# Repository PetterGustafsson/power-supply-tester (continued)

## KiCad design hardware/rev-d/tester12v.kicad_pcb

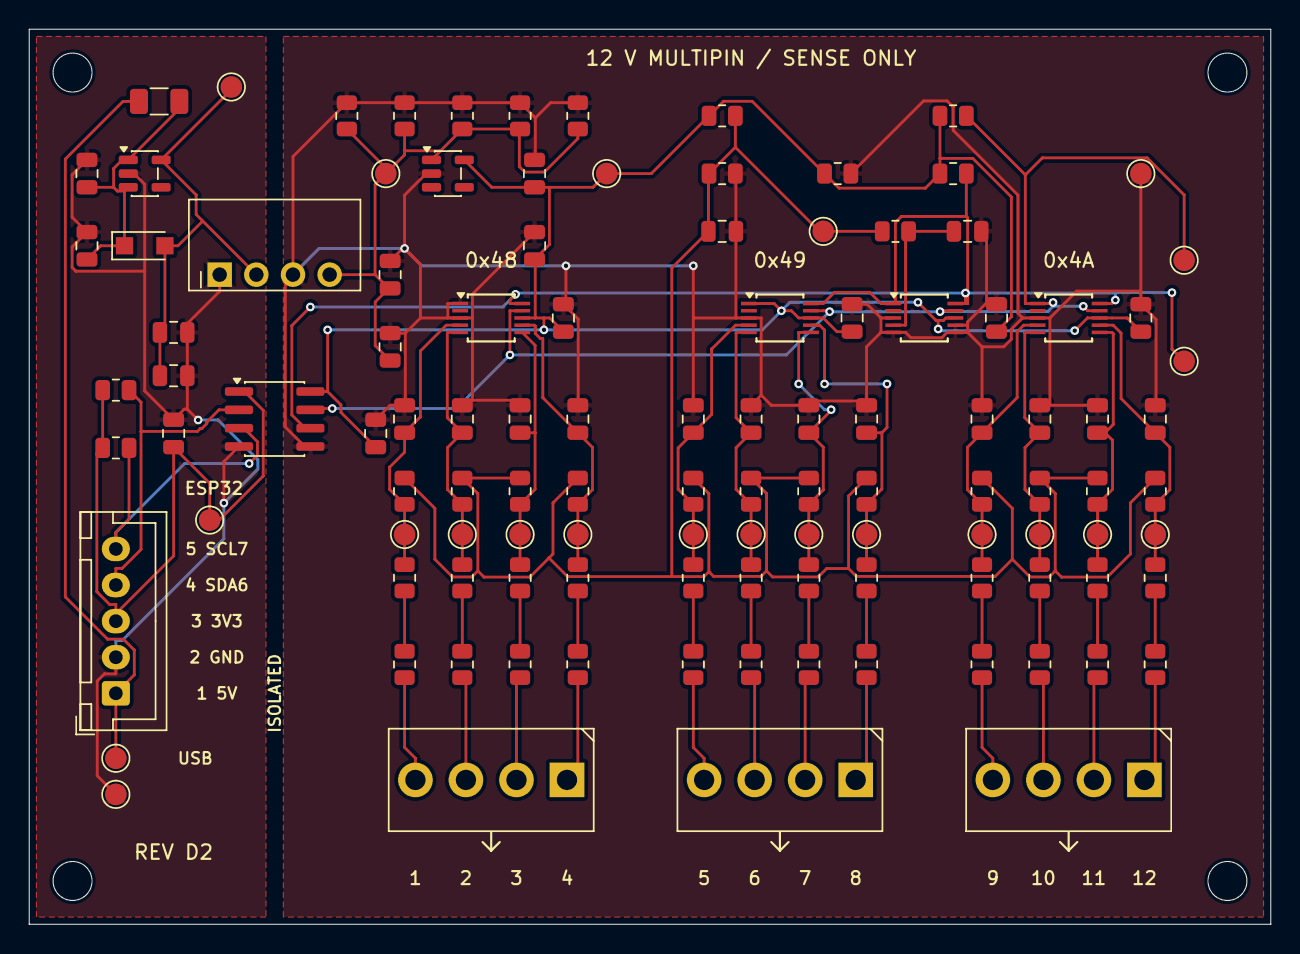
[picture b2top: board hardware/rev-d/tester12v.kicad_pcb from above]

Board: 2 copper layers, 86.0 x 62.0 mm, 117 parts (0 on the bottom side), 50 nets.

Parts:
C1, C2, C3, C4, C5, C6, C7, C8, C9, C10, C11, C12, C26, C28: 470p; C_0805_2012Metric
C13, C14, C15, C17, C19, C21, C23, C24, C25, C27: 100n; C_0805_2012Metric
C16, C18, C20, C22: 10u; C_0805_2012Metric
D1: LDO reverse protection; Nexperia_CFP3_SOD-123W
F1: 250mA PTC; Fuse_1206_3216Metric
H1, H2, H3, H4: MountingHole_2.7mm_M2.5
J1: INPUTS 1-4; XY350V_3.5_4P
J2: INPUTS 5-8; XY350V_3.5_4P
J3: INPUTS 9-12; XY350V_3.5_4P
J4: DISPLAY HARNESS; JST_XH_B5B-XH-A_1x05_P2.50mm_Vertical
R1, R2, R4, R5, R7, R8, R10, R11, R13, R14, R16, R17, R19, R20, R22, R23, R25, R26, R28, R29, R31, R32, R34, R35: 1M; R_0805_2012Metric
R3, R6, R9, R12, R15, R18, R21, R24, R27, R30, R33, R36, R37, R44, R45, R46, R47, R49: 4.7k; R_0805_2012Metric
R38, R39, R40, R41, R42, R43, R48: 1k; R_0805_2012Metric
TP1: A1; TestPoint_Pad_D1.5mm
TP2: A2; TestPoint_Pad_D1.5mm
TP3: A3; TestPoint_Pad_D1.5mm
TP4: A4; TestPoint_Pad_D1.5mm
TP5: A5; TestPoint_Pad_D1.5mm
TP6: A6; TestPoint_Pad_D1.5mm
TP7: A7; TestPoint_Pad_D1.5mm
TP8: A8; TestPoint_Pad_D1.5mm
TP9: A9; TestPoint_Pad_D1.5mm
TP10: A10; TestPoint_Pad_D1.5mm
TP11: A11; TestPoint_Pad_D1.5mm
TP12: A12; TestPoint_Pad_D1.5mm
TP13: USB5V; TestPoint_Pad_D1.5mm
TP14: USB_GND; TestPoint_Pad_D1.5mm
TP15: HOST3V3; TestPoint_Pad_D1.5mm
TP16: P3V3; TestPoint_Pad_D1.5mm
TP17: ISO5V_RAW; TestPoint_Pad_D1.5mm
TP18: A3V3; TestPoint_Pad_D1.5mm
TP19: AGND; TestPoint_Pad_D1.5mm
TP20: VBIAS; TestPoint_Pad_D1.5mm
TP21: SDA_ISO; TestPoint_Pad_D1.5mm
TP22: SCL_ISO; TestPoint_Pad_D1.5mm
U1, U2, U3, U8: ADS1115IDGSR; TSSOP-10_3x3mm_P0.5mm
U4: TLV75533PDBVR; SOT-23-5
U5: TPS70933DBVR; SOT-23-5
U6: ISO1640BDR; SOIC-8_3.9x4.9mm_P1.27mm
U7: B0305S-1WR3; B0305S_1WR3_EVISUN

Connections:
A1: C1.1, R2.2, R3.1, TP1.1, U1.4
A2: C2.1, R5.2, R6.1, TP2.1, U1.5
A3: C3.1, R8.2, R9.1, TP3.1, U1.6
A3V3: C13.1, C14.1, C15.1, C22.1, C23.1, C25.1, C27.1, R37.1, R44.1, R45.1, R48.1, TP18.1, U1.8, U2.1, U2.8, U3.8, U5.5, U6.8, U8.8
A4: C4.1, R11.2, R12.1, TP4.1, U1.7
A5: C5.1, R14.2, R15.1, TP5.1, U2.4
A6: C6.1, R17.2, R18.1, TP6.1, U2.5
A7: C7.1, R20.2, R21.1, TP7.1, U2.6
A8: C8.1, R23.2, R24.1, TP8.1, U2.7
A9: C9.1, R26.2, R27.1, TP9.1, U3.4
A10: C10.1, R29.2, R30.1, TP10.1, U3.5
A11: C11.1, R32.2, R33.1, TP11.1, U3.6
A12: C12.1, R35.2, R36.1, TP12.1, U3.7
AGND: C1.2, C2.2, C3.2, C4.2, C5.2, C6.2, C7.2, C8.2, C9.2, C10.2, C11.2, C12.2, C13.2, C14.2, C15.2, C20.2, C21.2, C22.2, C23.2, C25.2, C26.2, C27.2, C28.2, R38.2, R39.2, R40.2, R41.2, R42.2, R43.2, R48.2, TP19.1, U1.1, U1.3, U2.3, U3.3, U5.2, U6.5, U7.3, U8.3, U8.5, U8.6, U8.7
HOST3V3: C24.1, J4.3, R46.1, R47.1, TP15.1, U6.1
ISO5V_RAW: C20.1, C21.1, R39.1, R40.1, R41.1, R42.1, R43.1, TP17.1, U5.1, U7.4
MID1: R1.2, R2.1
MID2: R4.2, R5.1
MID3: R7.2, R8.1
MID4: R10.2, R11.1
MID5: R13.2, R14.1
MID6: R16.2, R17.1
MID7: R19.2, R20.1
MID8: R22.2, R23.1
MID9: R25.2, R26.1
MID10: R28.2, R29.1
MID11: R31.2, R32.1
MID12: R34.2, R35.1
P1: J1.4, R1.1
P2: J1.3, R4.1
P3: J1.2, R7.1
P3V3: C18.1, C19.1, D1.2, TP16.1, U4.5, U7.2
P4: J1.1, R10.1
P5: J2.4, R13.1
P6: J2.3, R16.1
P7: J2.2, R19.1
P8: J2.1, R22.1
P9: J3.4, R25.1
P10: J3.3, R28.1
P11: J3.2, R31.1
P12: J3.1, R34.1
REF_ADC: C28.1, R49.2, U8.4
SCL_HOST: J4.5, R47.2, U6.3
SCL_ISO: R45.2, TP22.1, U1.10, U2.10, U3.10, U6.6, U8.1, U8.10
SDA_HOST: J4.4, R46.2, U6.2
SDA_ISO: R44.2, TP21.1, U1.9, U2.9, U3.1, U3.9, U6.7, U8.9
USB5V: F1.1, J4.1, TP13.1
USB5V_F: C16.1, C17.1, D1.1, F1.2, U4.1, U4.3
USB_GND: C16.2, C17.2, C18.2, C19.2, C24.2, J4.2, TP14.1, U4.2, U6.4, U7.1
VBIAS: C26.1, R3.2, R6.2, R9.2, R12.2, R15.2, R18.2, R21.2, R24.2, R27.2, R30.2, R33.2, R36.2, R37.2, R38.1, R49.1, TP20.1

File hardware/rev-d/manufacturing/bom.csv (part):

Reference,Value,Manufacturer,MPN,Footprint,Populate,Notes,LCSC,JLC Category
J1,INPUTS 1-4,Ningbo Xinlaiya Elec.,XY350V-3.5-4P,Tester:XY350V_3.5_4P,YES,"C557656; 3.5mm pitch, 0.8mm square pins, 1.4mm drill. 14x6.9mm body. WIRE OPENINGS FACE LOWER BOARD EDGE (+Y); footprint contact 1 at right. Input labels increase left-to-right.",C557656,Extended
R1,1M,UNI-ROYAL,0805W8F1004T5E,Tester:R_0805_2012Metric,YES,1%,C17514,Basic
R2,1M,UNI-ROYAL,0805W8F1004T5E,Tester:R_0805_2012Metric,YES,1%,C17514,Basic
R3,4.7k,UNI-ROYAL,0805W8F4701T5E,Tester:R_0805_2012Metric,YES,"1% | JLC: Basic; same 1%, 100ppm/K, 125mW, 150V rating",C17673,Basic
C1,470p,Fenghua,0805B471K500NT,Tester:C_0805_2012Metric,YES,"470pF +/-10%, 50V X7R; Rev D candidate model bounds total input capacitance at 1nF",C1743,Basic
R4,1M,UNI-ROYAL,0805W8F1004T5E,Tester:R_0805_2012Metric,YES,1%,C17514,Basic
R5,1M,UNI-ROYAL,0805W8F1004T5E,Tester:R_0805_2012Metric,YES,1%,C17514,Basic
R6,4.7k,UNI-ROYAL,0805W8F4701T5E,Tester:R_0805_2012Metric,YES,"1% | JLC: Basic; same 1%, 100ppm/K, 125mW, 150V rating",C17673,Basic
C2,470p,Fenghua,0805B471K500NT,Tester:C_0805_2012Metric,YES,"470pF +/-10%, 50V X7R; Rev D candidate model bounds total input capacitance at 1nF",C1743,Basic
R7,1M,UNI-ROYAL,0805W8F1004T5E,Tester:R_0805_2012Metric,YES,1%,C17514,Basic
R8,1M,UNI-ROYAL,0805W8F1004T5E,Tester:R_0805_2012Metric,YES,1%,C17514,Basic
R9,4.7k,UNI-ROYAL,0805W8F4701T5E,Tester:R_0805_2012Metric,YES,"1% | JLC: Basic; same 1%, 100ppm/K, 125mW, 150V rating",C17673,Basic
C3,470p,Fenghua,0805B471K500NT,Tester:C_0805_2012Metric,YES,"470pF +/-10%, 50V X7R; Rev D candidate model bounds total input capacitance at 1nF",C1743,Basic
R10,1M,UNI-ROYAL,0805W8F1004T5E,Tester:R_0805_2012Metric,YES,1%,C17514,Basic
R11,1M,UNI-ROYAL,0805W8F1004T5E,Tester:R_0805_2012Metric,YES,1%,C17514,Basic
R12,4.7k,UNI-ROYAL,0805W8F4701T5E,Tester:R_0805_2012Metric,YES,"1% | JLC: Basic; same 1%, 100ppm/K, 125mW, 150V rating",C17673,Basic
C4,470p,Fenghua,0805B471K500NT,Tester:C_0805_2012Metric,YES,"470pF +/-10%, 50V X7R; Rev D candidate model bounds total input capacitance at 1nF",C1743,Basic
U1,ADS1115IDGSR,Texas Instruments,ADS1115IDGSR,Tester:TSSOP-10_3x3mm_P0.5mm,YES,"PGA +/-1.024V, nominal attenuation 426.5319. Rev D calibration/firmware required.",C37593,Extended
C13,100n,Yageo,CC0805KRX7R9BB104,Tester:C_0805_2012Metric,YES,"Use specified capacitance, voltage and dielectric | JLC: Basic; 100nF, 10%, 50V, X7R preserved",C49678,Basic
J2,INPUTS 5-8,Ningbo Xinlaiya Elec.,XY350V-3.5-4P,Tester:XY350V_3.5_4P,YES,"C557656; 3.5mm pitch, 0.8mm square pins, 1.4mm drill. 14x6.9mm body. WIRE OPENINGS FACE LOWER BOARD EDGE (+Y); footprint contact 1 at right. Input labels increase left-to-right.",C557656,Extended
R13,1M,UNI-ROYAL,0805W8F1004T5E,Tester:R_0805_2012Metric,YES,1%,C17514,Basic
R14,1M,UNI-ROYAL,0805W8F1004T5E,Tester:R_0805_2012Metric,YES,1%,C17514,Basic
R15,4.7k,UNI-ROYAL,0805W8F4701T5E,Tester:R_0805_2012Metric,YES,"1% | JLC: Basic; same 1%, 100ppm/K, 125mW, 150V rating",C17673,Basic
C5,470p,Fenghua,0805B471K500NT,Tester:C_0805_2012Metric,YES,"470pF +/-10%, 50V X7R; Rev D candidate model bounds total input capacitance at 1nF",C1743,Basic
R16,1M,UNI-ROYAL,0805W8F1004T5E,Tester:R_0805_2012Metric,YES,1%,C17514,Basic
R17,1M,UNI-ROYAL,0805W8F1004T5E,Tester:R_0805_2012Metric,YES,1%,C17514,Basic
R18,4.7k,UNI-ROYAL,0805W8F4701T5E,Tester:R_0805_2012Metric,YES,"1% | JLC: Basic; same 1%, 100ppm/K, 125mW, 150V rating",C17673,Basic
C6,470p,Fenghua,0805B471K500NT,Tester:C_0805_2012Metric,YES,"470pF +/-10%, 50V X7R; Rev D candidate model bounds total input capacitance at 1nF",C1743,Basic
R19,1M,UNI-ROYAL,0805W8F1004T5E,Tester:R_0805_2012Metric,YES,1%,C17514,Basic
R20,1M,UNI-ROYAL,0805W8F1004T5E,Tester:R_0805_2012Metric,YES,1%,C17514,Basic
R21,4.7k,UNI-ROYAL,0805W8F4701T5E,Tester:R_0805_2012Metric,YES,"1% | JLC: Basic; same 1%, 100ppm/K, 125mW, 150V rating",C17673,Basic
C7,470p,Fenghua,0805B471K500NT,Tester:C_0805_2012Metric,YES,"470pF +/-10%, 50V X7R; Rev D candidate model bounds total input capacitance at 1nF",C1743,Basic
R22,1M,UNI-ROYAL,0805W8F1004T5E,Tester:R_0805_2012Metric,YES,1%,C17514,Basic
R23,1M,UNI-ROYAL,0805W8F1004T5E,Tester:R_0805_2012Metric,YES,1%,C17514,Basic
R24,4.7k,UNI-ROYAL,0805W8F4701T5E,Tester:R_0805_2012Metric,YES,"1% | JLC: Basic; same 1%, 100ppm/K, 125mW, 150V rating",C17673,Basic
C8,470p,Fenghua,0805B471K500NT,Tester:C_0805_2012Metric,YES,"470pF +/-10%, 50V X7R; Rev D candidate model bounds total input capacitance at 1nF",C1743,Basic
U2,ADS1115IDGSR,Texas Instruments,ADS1115IDGSR,Tester:TSSOP-10_3x3mm_P0.5mm,YES,"PGA +/-1.024V, nominal attenuation 426.5319. Rev D calibration/firmware required.",C37593,Extended
C14,100n,Yageo,CC0805KRX7R9BB104,Tester:C_0805_2012Metric,YES,"Use specified capacitance, voltage and dielectric | JLC: Basic; 100nF, 10%, 50V, X7R preserved",C49678,Basic
J3,INPUTS 9-12,Ningbo Xinlaiya Elec.,XY350V-3.5-4P,Tester:XY350V_3.5_4P,YES,"C557656; 3.5mm pitch, 0.8mm square pins, 1.4mm drill. 14x6.9mm body. WIRE OPENINGS FACE LOWER BOARD EDGE (+Y); footprint contact 1 at right. Input labels increase left-to-right.",C557656,Extended
R25,1M,UNI-ROYAL,0805W8F1004T5E,Tester:R_0805_2012Metric,YES,1%,C17514,Basic
R26,1M,UNI-ROYAL,0805W8F1004T5E,Tester:R_0805_2012Metric,YES,1%,C17514,Basic
R27,4.7k,UNI-ROYAL,0805W8F4701T5E,Tester:R_0805_2012Metric,YES,"1% | JLC: Basic; same 1%, 100ppm/K, 125mW, 150V rating",C17673,Basic
C9,470p,Fenghua,0805B471K500NT,Tester:C_0805_2012Metric,YES,"470pF +/-10%, 50V X7R; Rev D candidate model bounds total input capacitance at 1nF",C1743,Basic
R28,1M,UNI-ROYAL,0805W8F1004T5E,Tester:R_0805_2012Metric,YES,1%,C17514,Basic
R29,1M,UNI-ROYAL,0805W8F1004T5E,Tester:R_0805_2012Metric,YES,1%,C17514,Basic
R30,4.7k,UNI-ROYAL,0805W8F4701T5E,Tester:R_0805_2012Metric,YES,"1% | JLC: Basic; same 1%, 100ppm/K, 125mW, 150V rating",C17673,Basic
C10,470p,Fenghua,0805B471K500NT,Tester:C_0805_2012Metric,YES,"470pF +/-10%, 50V X7R; Rev D candidate model bounds total input capacitance at 1nF",C1743,Basic
R31,1M,UNI-ROYAL,0805W8F1004T5E,Tester:R_0805_2012Metric,YES,1%,C17514,Basic
R32,1M,UNI-ROYAL,0805W8F1004T5E,Tester:R_0805_2012Metric,YES,1%,C17514,Basic
R33,4.7k,UNI-ROYAL,0805W8F4701T5E,Tester:R_0805_2012Metric,YES,"1% | JLC: Basic; same 1%, 100ppm/K, 125mW, 150V rating",C17673,Basic
C11,470p,Fenghua,0805B471K500NT,Tester:C_0805_2012Metric,YES,"470pF +/-10%, 50V X7R; Rev D candidate model bounds total input capacitance at 1nF",C1743,Basic
R34,1M,UNI-ROYAL,0805W8F1004T5E,Tester:R_0805_2012Metric,YES,1%,C17514,Basic
R35,1M,UNI-ROYAL,0805W8F1004T5E,Tester:R_0805_2012Metric,YES,1%,C17514,Basic
R36,4.7k,UNI-ROYAL,0805W8F4701T5E,Tester:R_0805_2012Metric,YES,"1% | JLC: Basic; same 1%, 100ppm/K, 125mW, 150V rating",C17673,Basic
C12,470p,Fenghua,0805B471K500NT,Tester:C_0805_2012Metric,YES,"470pF +/-10%, 50V X7R; Rev D candidate model bounds total input capacitance at 1nF",C1743,Basic
U3,ADS1115IDGSR,Texas Instruments,ADS1115IDGSR,Tester:TSSOP-10_3x3mm_P0.5mm,YES,"PGA +/-1.024V, nominal attenuation 426.5319. Rev D calibration/firmware required.",C37593,Extended
C15,100n,Yageo,CC0805KRX7R9BB104,Tester:C_0805_2012Metric,YES,"Use specified capacitance, voltage and dielectric | JLC: Basic; 100nF, 10%, 50V, X7R preserved",C49678,Basic
J4,DISPLAY HARNESS,JST,B5B-XH-A(LF)(SN),Tester:JST_XH_B5B-XH-A_1x05_P2.50mm_Vertical,YES,"1=VSYS/5V,2=GND,3=3V3,4=GPIO6 SDA,5=GPIO7 SCL. One USB cable to Waveshare powers both boards.",C157991,Extended
U4,TLV75533PDBVR,Texas Instruments,TLV75533PDBVR,Tester:SOT-23-5,YES,Primary 3.3V preregulator avoids 4.5V minimum requirement at USB-fed isolated converter. 500mA rating.,C404027,Extended
U5,TPS70933DBVR,Texas Instruments,TPS70933DBVR,Tester:SOT-23-5,YES,"30V VIN withstands unregulated converter output. EN intentionally floating, internally enabled; do not tie to VIN. Integrated reverse-current blocking.",C89347,Extended
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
